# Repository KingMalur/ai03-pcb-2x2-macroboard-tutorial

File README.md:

# ai03-pcb-2x2-macroboard-tutorial
See https://wiki.ai03.com/books/pcb-design/chapter/pcb-designer-guide for details.

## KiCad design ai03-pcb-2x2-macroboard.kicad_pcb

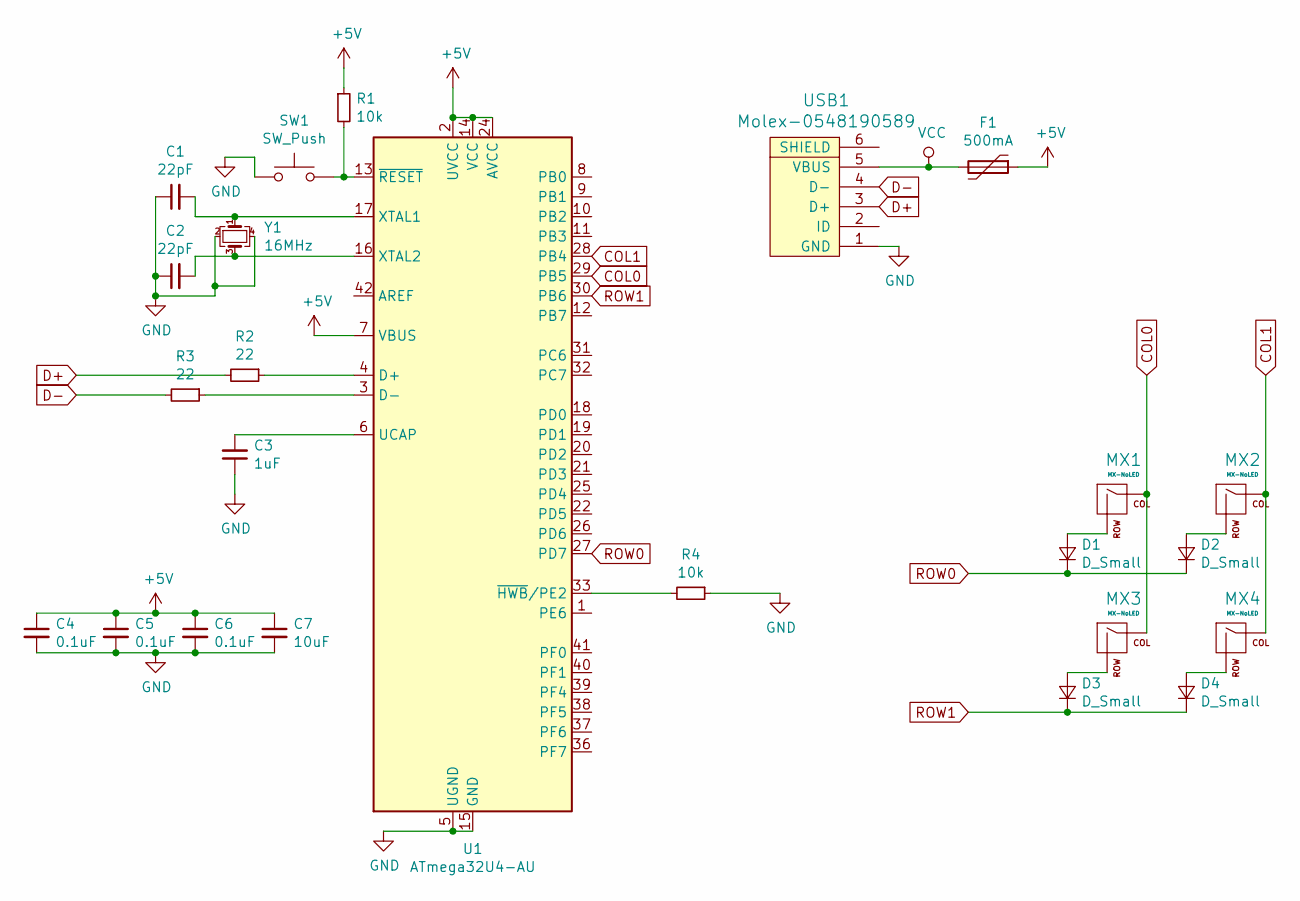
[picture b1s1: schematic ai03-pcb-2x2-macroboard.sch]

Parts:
C1, C2: 22pF; C_0805_2012Metric
C3: 1uF; C_0805_2012Metric
C4, C5, C6: 0.1uF; C_0805_2012Metric
C7: 10uF; C_0805_2012Metric
D1, D2, D3, D4: D_Small; D_SOD-123
F1: 500mA; Fuse_1206_3216Metric
MX1, MX2, MX3, MX4: MX-NoLED; MX-1U
R1, R4: 10k; R_0805_2012Metric
R2, R3: 22; R_0805_2012Metric
SW1: SW_Push; SKQG-1155865
U1: ATmega32U4-AU; TQFP-44_10x10mm_P0.8mm
USB1: Molex-0548190589
Y1: 16MHz; Crystal_SMD_3225-4Pin_3.2x2.5mm

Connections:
+5V: C4.1, C5.1, C6.1, C7.1, F1.1, R1.1, U1.2 (UVCC), U1.7 (VBUS), U1.14 (VCC), U1.24 (AVCC), U1.34 (VCC), U1.44 (AVCC)
COL0: MX1.1 (COL), MX3.1 (COL), U1.29 (PB5)
COL1: MX2.1 (COL), MX4.1 (COL), U1.28 (PB4)
D+: R2.2, USB1.3 (D+)
D-: R3.2, USB1.4 (D-)
GND: C1.1, C2.1, C3.1, C4.2, C5.2, C6.2, C7.2, R4.1, SW1.1, U1.5 (UGND), U1.15 (GND), U1.23 (GND), U1.35 (GND), U1.43 (GND), USB1.1 (GND), Y1.2, Y1.4
unnamed: C1.2, U1.17 (XTAL1), Y1.1
unnamed: C2.2, U1.16 (XTAL2), Y1.3
unnamed: C3.2, U1.6 (UCAP)
unnamed: D1.2 (A), MX1.2 (ROW)
unnamed: D2.2 (A), MX2.2 (ROW)
unnamed: D3.2 (A), MX3.2 (ROW)
unnamed: D4.2 (A), MX4.2 (ROW)
unnamed: R1.2, SW1.2, U1.13 (~RESET)
unnamed: R2.1, U1.4 (D+)
unnamed: R3.1, U1.3 (D-)
unnamed: R4.2, U1.33 (~HWB~/PE2)
ROW0: D1.1 (K), D2.1 (K), U1.27 (PD7)
ROW1: D3.1 (K), D4.1 (K), U1.30 (PB6)
VCC: F1.2, USB1.5 (VBUS)

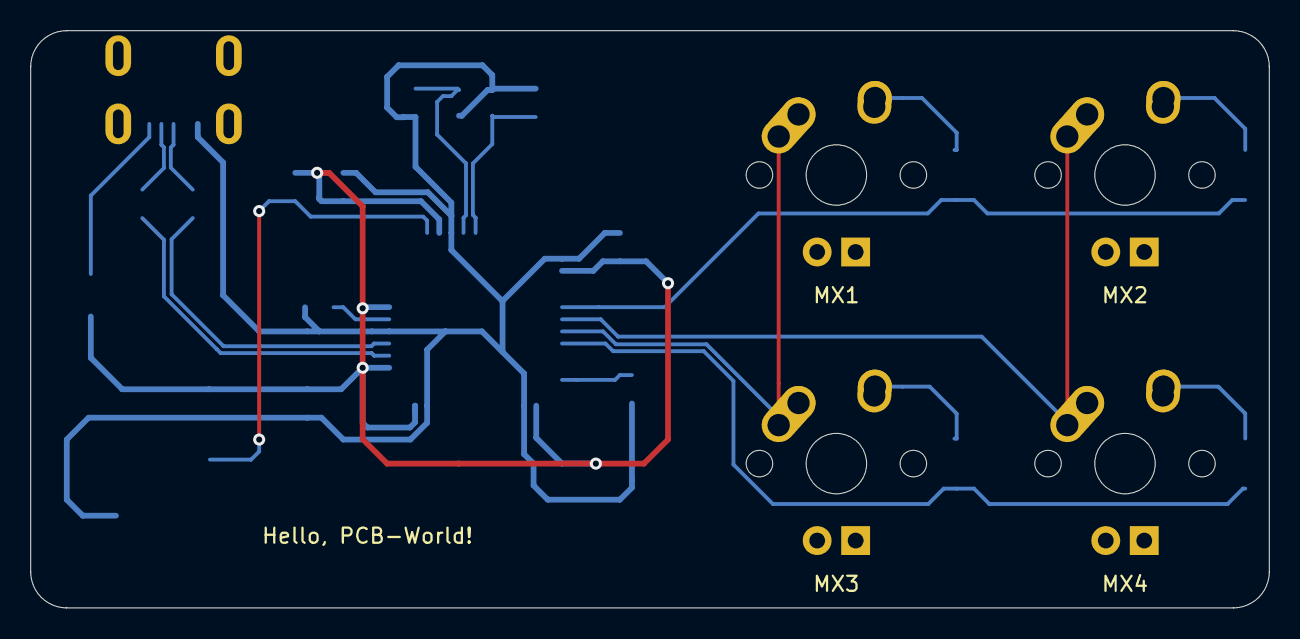
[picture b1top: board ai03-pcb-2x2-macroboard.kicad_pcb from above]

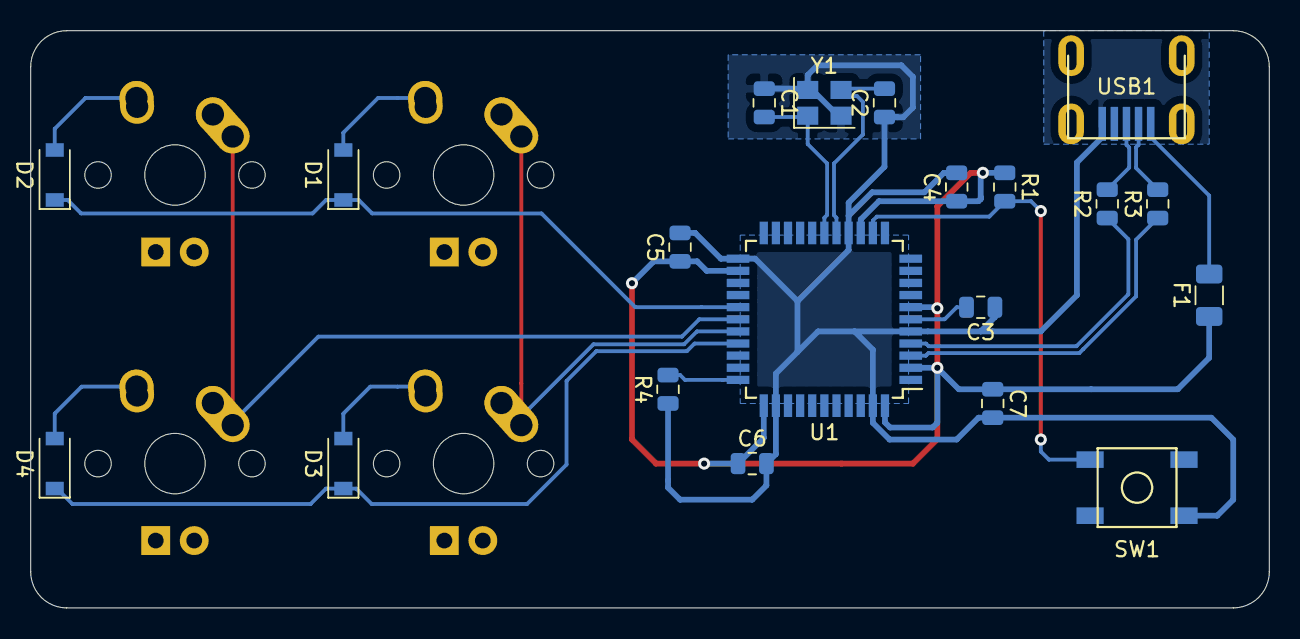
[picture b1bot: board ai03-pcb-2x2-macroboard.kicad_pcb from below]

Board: 2 copper layers, 81.8 x 38.1 mm, 24 parts (20 on the bottom side), 20 nets.

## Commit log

2020-07-28 Add KiCAD-project
2020-07-28 Add Sudmodules
2020-07-28 Add Libraries
2020-07-28 Add MCU zone
2020-07-28 Add MX-Matrix
2020-07-28 Add footprints
2020-07-28 Add MCU to PCB
2020-07-28 Place Components
2020-07-29 Update Cache
2020-07-29 Update Schematic
    I forgot some labels etc. so here they are.
2020-07-29 Re-Place Components
    Placement was too bad -> Do it again!
2020-07-29 Add Routing
2020-07-29 Add Gerber-Files
